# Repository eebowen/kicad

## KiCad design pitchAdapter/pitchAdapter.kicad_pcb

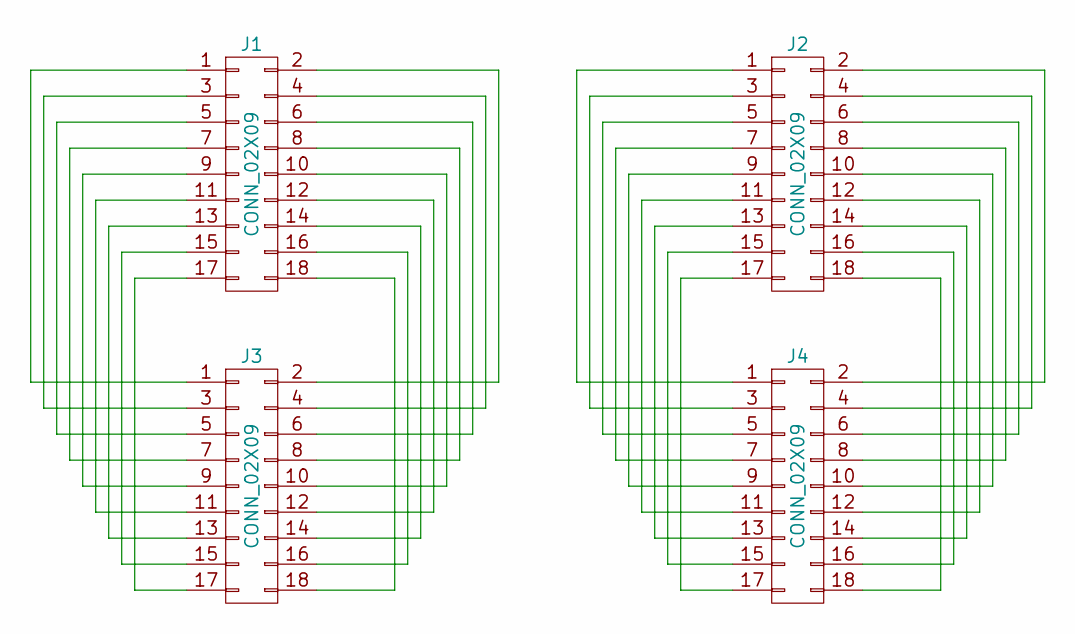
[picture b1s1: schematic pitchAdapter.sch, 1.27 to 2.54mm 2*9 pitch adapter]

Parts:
J1: CONN_02X09; Socket_Strip_Straight_2x09_Pitch2.00mm
J2: CONN_02X09; Pin_Header_Straight_2x09_Pitch2.00mm
J3: CONN_02X09; Socket_Strip_Straight_2x09_Pitch2.54mm
J4: CONN_02X09; Pin_Header_Straight_2x09_Pitch2.54mm

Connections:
unnamed: J1.1, J3.1
unnamed: J1.2, J3.2
unnamed: J1.3, J3.3
unnamed: J1.4, J3.4
unnamed: J1.5, J3.5
unnamed: J1.6, J3.6
unnamed: J1.7, J3.7
unnamed: J1.8, J3.8
unnamed: J1.9, J3.9
unnamed: J1.10, J3.10
unnamed: J1.11, J3.11
unnamed: J1.12, J3.12
unnamed: J1.13, J3.13
unnamed: J1.14, J3.14
unnamed: J1.15, J3.15
unnamed: J1.16, J3.16
unnamed: J1.17, J3.17
unnamed: J1.18, J3.18
unnamed: J2.1, J4.1
unnamed: J2.2, J4.2
unnamed: J2.3, J4.3
unnamed: J2.4, J4.4
unnamed: J2.5, J4.5
unnamed: J2.6, J4.6
unnamed: J2.7, J4.7
unnamed: J2.8, J4.8
unnamed: J2.9, J4.9
unnamed: J2.10, J4.10
unnamed: J2.11, J4.11
unnamed: J2.12, J4.12
unnamed: J2.13, J4.13
unnamed: J2.14, J4.14
unnamed: J2.15, J4.15
unnamed: J2.16, J4.16
unnamed: J2.17, J4.17
unnamed: J2.18, J4.18

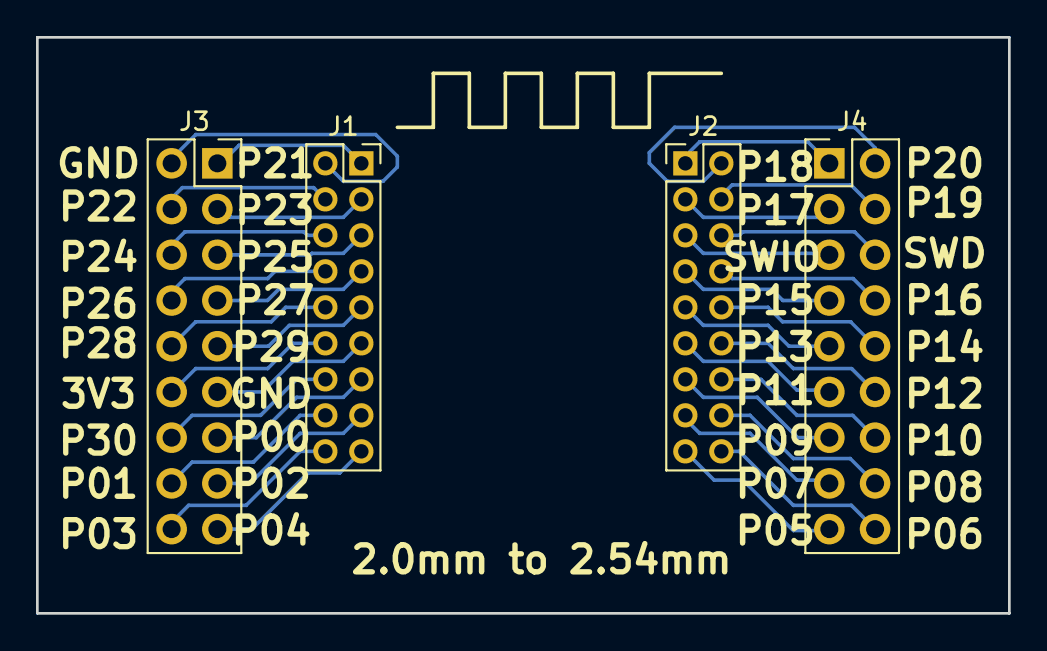
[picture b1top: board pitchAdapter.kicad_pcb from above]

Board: 2 copper layers, 54.0 x 32.0 mm, 4 parts (0 on the bottom side), 36 nets.

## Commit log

2017-06-13 test
2017-06-13 6/13
2017-06-16 Adpter V1 Done
2017-06-19 Adpter V1
